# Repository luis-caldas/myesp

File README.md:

# ESP

Collection of all ESPHome devices

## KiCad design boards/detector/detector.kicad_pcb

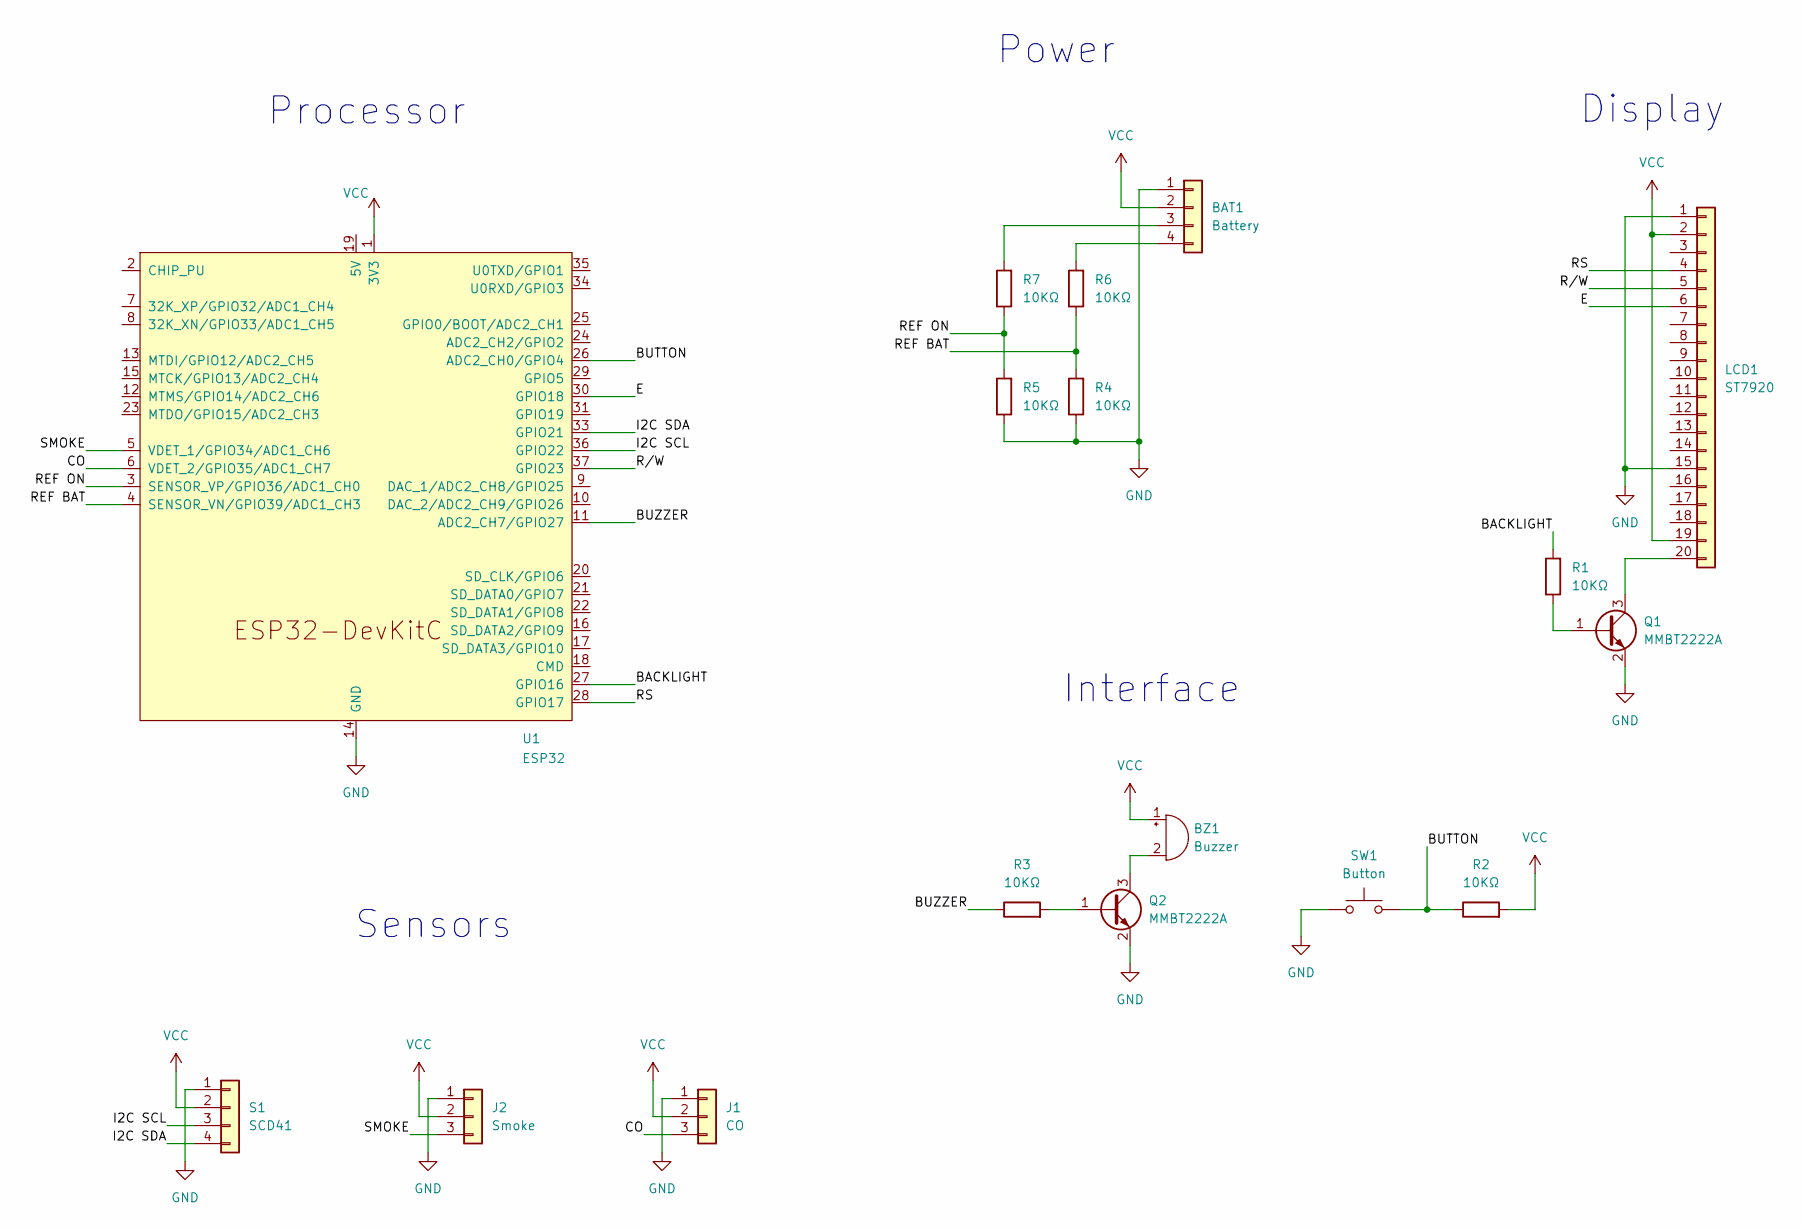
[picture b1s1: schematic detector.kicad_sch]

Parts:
BAT1: Battery; JST_XH_S4B-XH-A_1x04_P2.50mm_Horizontal
BZ1: Buzzer; Buzzer_TDK_PS1240P02BT_D12.2mm_H6.5mm
J1: CO; DFRobot Sensor
J2: Smoke; DFRobot Sensor
LCD1: ST7920
Q1, Q2: MMBT2222A; SOT-23
R1, R2, R3, R4, R5, R6, R7: 10KΩ; R_0805_2012Metric_Pad1.20x1.40mm_HandSolder
S1: SCD41
SW1: Button
U1: ESP32; ESP32-DevKitC

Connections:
/BACKLIGHT: R1.2, U1.27 (GPIO16)
/BUTTON: R2.1, SW1.2, U1.26 (ADC2_CH0/GPIO4)
/BUZZER: R3.1, U1.11 (ADC2_CH7/GPIO27)
/CO: J1.3 (A), U1.6 (VDET_2/GPIO35/ADC1_CH7)
/E: LCD1.6 (E), U1.30 (GPIO18)
/I2C SCL: S1.3 (SCL), U1.36 (GPIO22)
/I2C SDA: S1.4 (SDA), U1.33 (GPIO21)
/REF BAT: R4.2, R6.1, U1.4 (SENSOR_VN/GPIO39/ADC1_CH3)
/REF ON: R5.2, R7.1, U1.3 (SENSOR_VP/GPIO36/ADC1_CH0)
/RS: LCD1.4 (RS), U1.28 (GPIO17)
/R/W: LCD1.5 (R/W), U1.37 (GPIO23)
/SMOKE: J2.3 (A), U1.5 (VDET_1/GPIO34/ADC1_CH6)
GND: BAT1.1, J1.1 (GND), J2.1 (GND), LCD1.1 (GND), LCD1.15 (PSB), Q1.2 (E), Q2.2 (E), R4.1, R5.1, S1.1 (GND), SW1.1, U1.14 (GND), U1.32 (GND), U1.38 (GND)
unnamed: BAT1.3, R7.2
unnamed: BAT1.4, R6.2
unnamed: BZ1.2 (-), Q2.3 (C)
unnamed: LCD1.20 (BLK), Q1.3 (C)
unnamed: Q1.1 (B), R1.1
unnamed: Q2.1 (B), R3.2
VCC: BAT1.2, BZ1.1 (+), J1.2 (VCC), J2.2 (VCC), LCD1.2 (VCC), LCD1.19 (BLA), R2.2, S1.2 (VCC), U1.1 (3V3)

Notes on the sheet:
Display
Processor
Power
Sensors
Interface

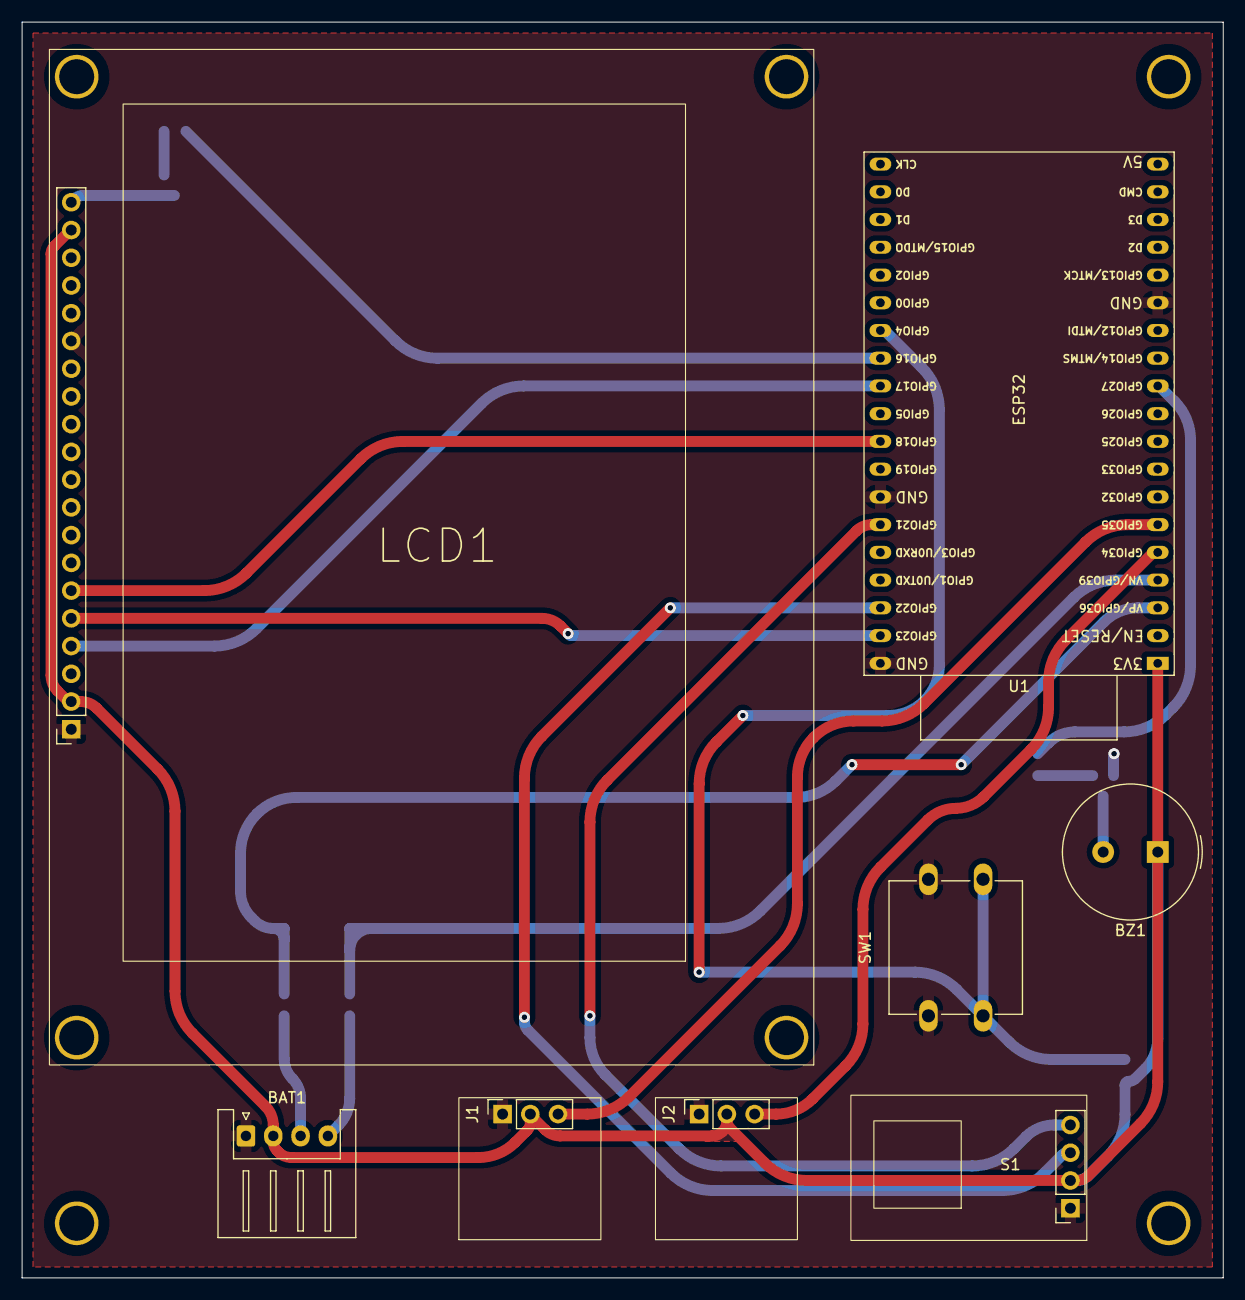
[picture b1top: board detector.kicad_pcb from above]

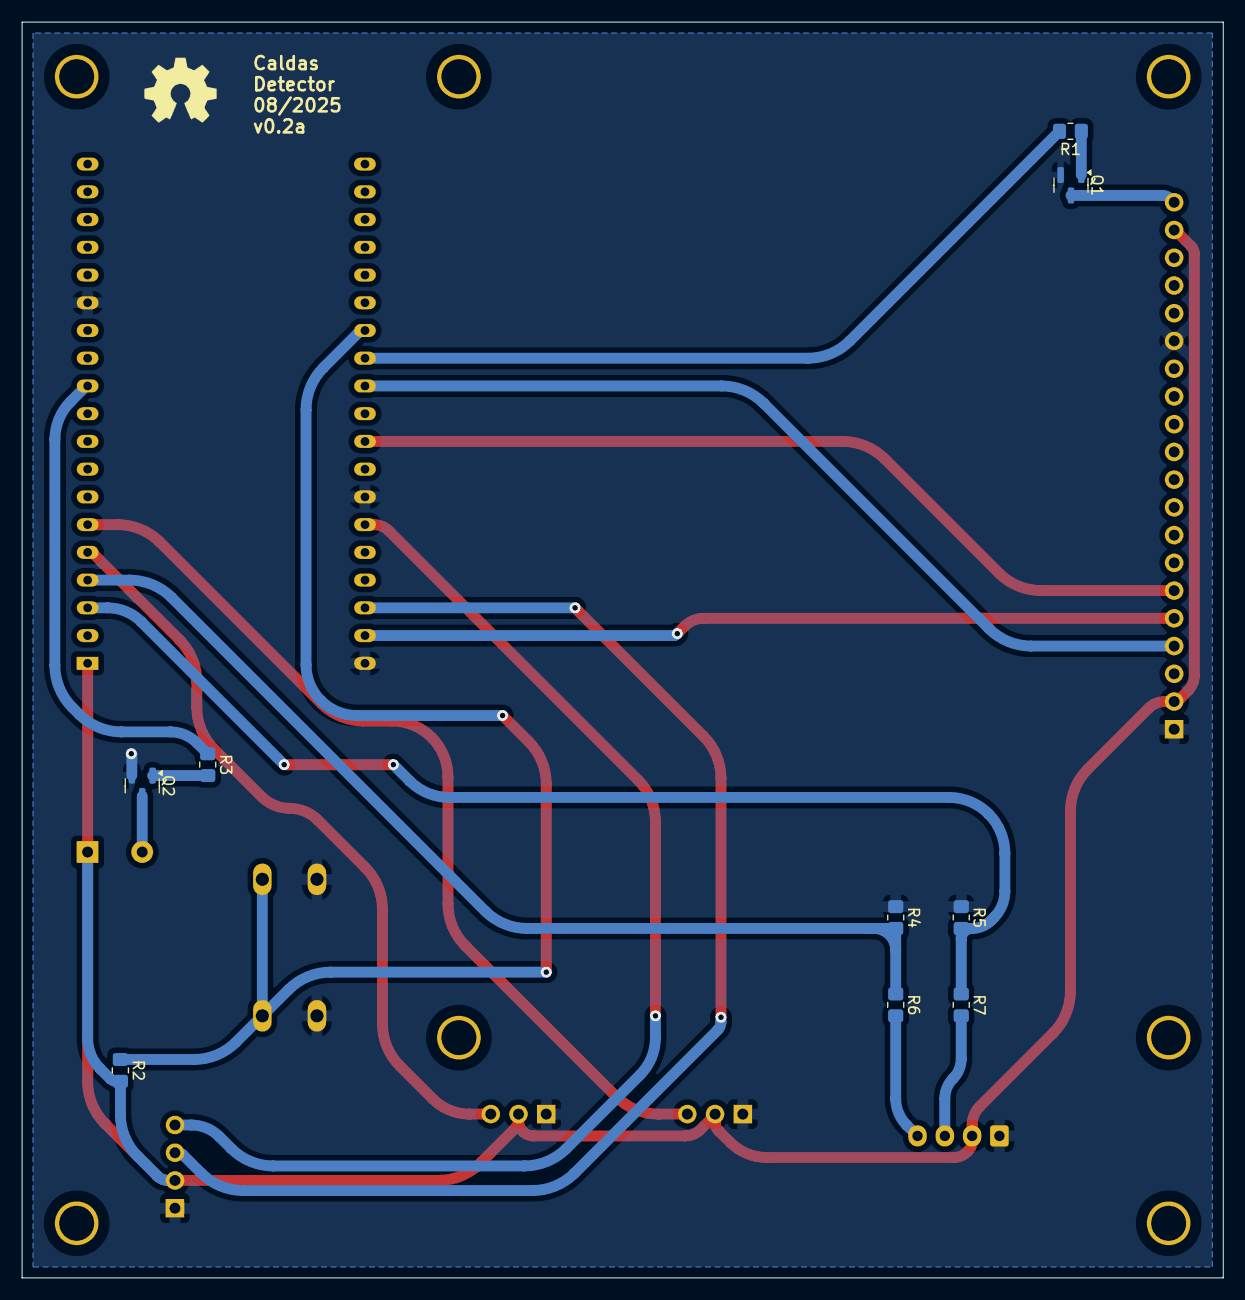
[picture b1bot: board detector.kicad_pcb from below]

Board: 2 copper layers, 110.0 x 115.0 mm, 17 parts (9 on the bottom side), 20 nets.

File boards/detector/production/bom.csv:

Designator,Footprint,Quantity,Value,LCSC Part #
BAT1,JST_XH_S4B-XH-A_1x04_P2.50mm_Horizontal,1,Battery,
BZ1,Buzzer_12x9.5RM7.6,1,Buzzer,
J1,DFRobot Sensor,1,CO,
J2,DFRobot Sensor,1,Smoke,
LCD1,ST7920,1,ST7920,
"Q1, Q2",SOT-23,2,MMBT2222A,
"R1, R2, R3",0805,3,10KΩ,
S1,SCD41,1,SCD41,
SW1,Button,1,Button,
U1,ESP32-DevKitC,1,ESP32,

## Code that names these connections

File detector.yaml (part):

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###############

spi:
  clk_pin: GPIO18   # E  - #6
  mosi_pin: GPIO23  # RW - #5
  interface: spi2

i2c:
  sda: GPIO21  # SDA
  scl: GPIO22  # SCL
  scan: true
  id: bus_a

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  - platform: gpio
    name: Button
    pin:
      number: GPIO4
      mode: INPUT_PULLUP
    internal: true
    on_press:
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output:

  - platform: ledc
    pin: GPIO16
    id: out_back

##########
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##########

  - platform: ledc
    pin: GPIO27
    id: buzzer

rtttl:
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  # #02	VCC	- VCC (5V)
  # #03 V0  - Not Needed (Regulated By Potentiometer Under Board)
  # #04	RS	- Any GPIO || CS (GPIO5)
  # #05	R/W	- MOSI (GPIO23)
  # #06	E	  - CLK (GPIO18)
  # #15	PSB	- GND (Enable SPI Mode)
  # #19	BLA	- Backlight
  # #20	BLK	- GND
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    rotation: 90
    update_interval: $screen_update
    cs_pin:
      number: GPIO17  # RS - #4
      inverted: true
    width: 128
    height: 64
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
  # Smoke
  - platform: adc
    pin: GPIO34
    id: smoke_voltage
    name: "Smoke Voltage"
    internal: true
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
  # CO
  - platform: adc
    pin: GPIO35
    id: co_voltage
    name: "Carbon Monoxide Voltage"
    internal: true
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
  # Input
  - platform: adc
    pin: GPIO36
    id: input_voltage
    name: "Input Voltage"
    internal: true
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  - platform: adc
    id: battery_voltage
    name: "Battery Voltage"
    pin: GPIO39
    internal: true
    attenuation: auto
    filters:
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
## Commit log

2024-12-08 first commit
    set up a remote controller device
2024-12-08 added hdmi switch to the remote codes
2024-12-08 added roku to the list of devices
2024-12-08 changed the default action on transmit to a script
2024-12-08 fixed spacing on scripts
2024-12-08 added readme
2024-12-08 fixed naming of some ha buttons
2024-12-08 renamed remote file
2024-12-08 added remote codes to their own file
2024-12-08 added a new samsung device
2024-12-08 changed the menu icons for roku
2024-12-08 fixed roku select code
2024-12-08 added new device
2024-12-08 removed the ir dumping
2024-12-08 added extra sensors
2024-12-08 changed the name of some diagnostics
2024-12-08 upgraded and modularised extra functions
2024-12-08 updated extras to remove redundant information
2024-12-08 added a sample file for a smart socket
2024-12-08 fixed some spacings
2024-12-09 changed the name of the extras file
2024-12-09 add a sample detector
2024-12-09 changed how packages are included
2024-12-09 made connection information common
    also added substitutions
2024-12-09 updated button and backlight integration detector
2024-12-10 changed the button dettection on detector
2024-12-10 added receiver codes
2024-12-11 added new sensor to detector
2024-12-11 updated display to show sensor information
2024-12-25 updated api password to encryption key
2024-12-25 added buzzer to detector
2024-12-26 moved specific remote hardware into shared package
2024-12-26 somewhat working codes with given delay
2024-12-26 added codes to match new sender remotes
2024-12-26 added internal to binary sensor
2024-12-26 added friendly names for all devices
2025-07-20 dimmer working
2025-07-20 fixed socket
2025-07-20 added a new socket
2025-07-20 calibrated power sensors
2025-07-29 updated detector
    started work on its logic
2025-08-08 progress on detector
2025-08-08 added new dimmer device
2025-08-08 renamed dimmers
2025-08-09 fixed remote box
2025-08-09 fixed names for projector show and hide
2025-08-09 updated detectors logic for siren
    also started work on its battery system
2025-08-10 added a new adapter
2025-08-10 added a light
2025-08-10 added a secrets skeleton file
2025-08-10 added a switch
2025-08-10 removed unecessary common file
2025-08-10 changed the default light on switch
2025-08-18 added lights and fan to the remote receiver
2025-08-18 updated pins on detector
2025-08-18 added a new dimmer
2025-08-19 added more references pictures
2025-08-19 fixed strapped pins
2025-08-19 removed nan from display
2025-08-19 started work on the detector schematic
2025-08-19 testing detector schematic and pcb
2025-08-19 updated detector schematic
2025-08-19 compacting pcb and fixing sizes
2025-08-19 moved backlight to pwm control
2025-08-19 updated names of buzzer api
2025-08-19 more work done on the detector board
2025-08-19 removed production folder
2025-08-19 updated ignore for build files
2025-08-20 changed output folder for stl files
2025-08-20 added cases design
2025-08-20 updated case model
2025-08-20 moved multiple devices into single generic config
    fixed socket ota
2025-08-21 added current limit to power devices
2025-08-21 added a relay device
2025-08-21 added overcurrent notification
2025-08-21 flipped switch on relay
2025-08-25 candeo update
2025-08-25 enabled light on candeo
2025-08-26 updated detector schematic
    LCD pins
    sensing voltage dividers
    buzzer footprint
2025-08-26 fixed lcd footprint to correct dimensions
2025-08-26 libary update for lcd
2025-08-26 updated pcb to match
2025-08-27 mirrored pcb
2025-08-27 updated schematic
2025-08-27 fixed some mistakes on pcb
2025-08-28 getting r0 for sensors
2025-08-29 finished sensors in detector
2025-08-29 added all sensors to alert on detector
2025-08-30 changed clean air CO resistance
2025-08-31 changed default resistance values on detector
2025-08-31 added temperature cutoff to electrical switches
2025-08-31 fixed adapters internal temperature
